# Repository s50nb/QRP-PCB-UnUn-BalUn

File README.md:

# QRP PCB UnUn/BalUn

*Simple, small, light and portable.*

The main point of portable QRP operation is to be as light as possible, especially for those of us who enjoy SOTA and POTA activations. Its based off a well known design (If I knew who the original designer was I would credit him on the design). Modified to work both as a UnUn for EFHW and random wire antennas, as well as a 1:1 or 4:1 BalUn for regular or OCF dipoles or even loops if desired. 

For EFHW you can stack the toroids and wind 21 turn on them with a tap at the third turn for the RF connection. This should in theory give better efficiency and so not wasted power for heating. This is specially important for qrp radios do to low power output.

For those interested theres alot said about it here [SOTA Reflector efhw debate](https://reflector.sota.org.uk/t/a-sota-centric-end-fed-half-wave-antenna-part-1/24756/11)

I have also added STEP files for those of you who would like to 3d print different enclosures. 

BOM:

- FT50-43 ferrite toroid
- 1x 100nf 3kV ceramic THT capacitor 
- 1x BNC Right Angle PCB Jack Through Hole Bulkhead Rear Mount 50 Ohm Isolated (Amphenol 031-5486 for instance)
- 0.3mm(28AWG) or 0.5mm(24AWG) enameled copper wire (As long as you can wind 14 turns around the toroid, any size you have will do actually)

## 3D Render

## Schematic

## PCB

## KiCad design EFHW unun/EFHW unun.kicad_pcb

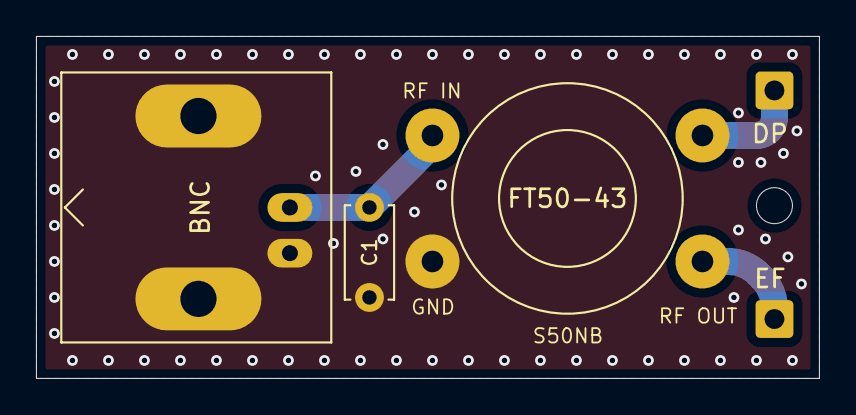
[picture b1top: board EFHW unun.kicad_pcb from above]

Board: 2 copper layers, 43.5 x 19.0 mm, 5 parts (0 on the bottom side), 4 nets.

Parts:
BNC: BNC_Amphenol_B6252HB-NPP3G-50_Horizontal
C1: 100 pF; C_Disc_D5.0mm_W2.5mm_P5.00mm
DP: Conn_01x01_Socket; SolderWire-0.5sqmm_1x01_D0.9mm_OD2.1mm
EF: Conn_01x01_Socket; SolderWire-0.5sqmm_1x01_D0.9mm_OD2.1mm
FT50-43: FT50 - 43; Transformer_Toroid_Horizontal_D12.5mm_Amidon-T44

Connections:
GND: BNC.2 (Ext), C1.2, FT50-43.1
unnamed: EF.1, FT50-43.2
unnamed: DP.1, FT50-43.4
unnamed: BNC.1 (In), C1.1, FT50-43.3

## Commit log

2025-01-22 QRP UnUn BalUn
2025-01-22 Fixed README
